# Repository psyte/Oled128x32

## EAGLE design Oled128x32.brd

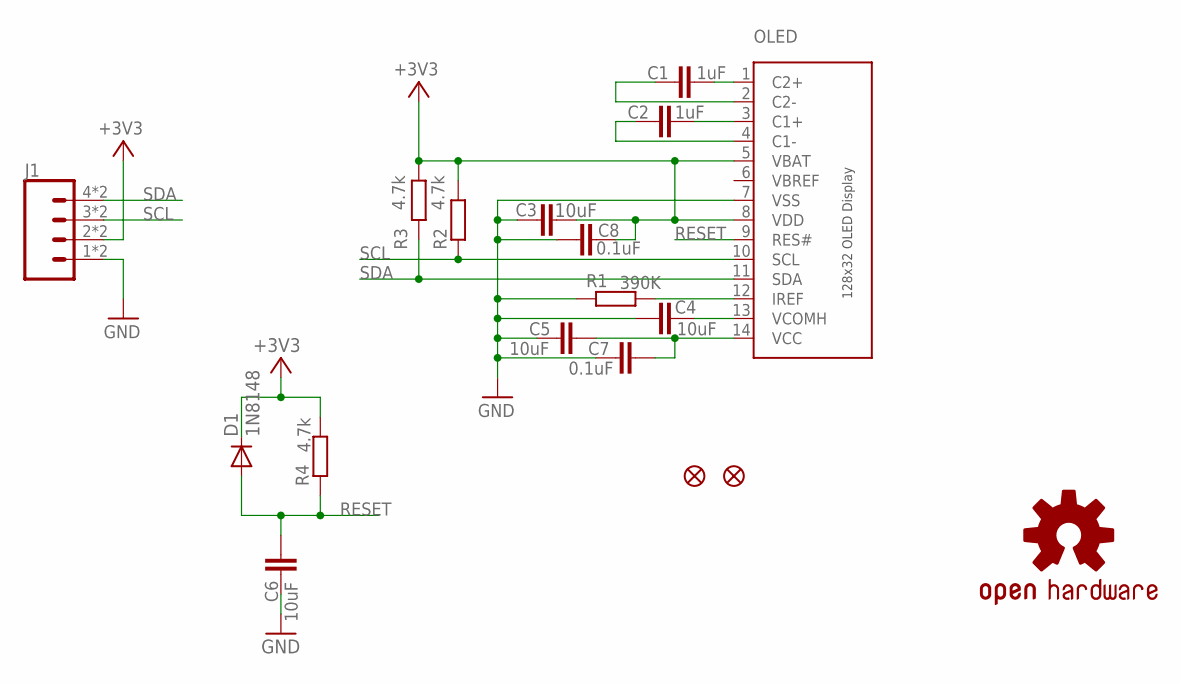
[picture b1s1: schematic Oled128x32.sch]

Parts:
C1, C2: 1uF; C0603
C3, C4, C5, C6: 10uF; C0603
C7, C8: 0.1uF; C0603
D1: 1N8148; SOD110-W
FD1, FD2: FIDUCIAL1X2; FIDUCIAL-1X2
J1: 1X04_SMD_STRAIGHT_COMBO; 1X04_SMD_VERTICAL_COMBO
LOGO1: OSHW-LOGOS; OSHW-LOGO-S
OLED: OLED_128X32_UG-2832HSWEG02; OLED_128X32_UG-2832HSWEG02_WRAPUNDER
R1: 390K; R0603
R2, R3, R4: 4.7k; R0603

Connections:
+3V3: C3.2, C8.2, D1.C, J1.2, J1.2-2 (2), OLED.5 (VBAT), OLED.8 (VDD), R2.2, R3.2, R4.2
GND: C3.1, C4.1, C5.1, C6.1, C7.1, C8.1, J1.1, J1.1-2 (1), OLED.7 (VSS), R1.1
unnamed: C1.2, OLED.1 (C2+)
unnamed: C1.1, OLED.2 (C2-)
unnamed: C2.2, OLED.3 (C1+)
unnamed: C2.1, OLED.4 (C1-)
unnamed: C4.2, OLED.13 (VCOMH)
unnamed: C5.2, C7.2, OLED.14 (VCC)
unnamed: OLED.12 (IREF), R1.2
RESET: C6.2, D1.A, OLED.9 (RES#), R4.1
SCL: J1.3, J1.3-2 (3), OLED.10 (SCL), R2.1
SDA: J1.4, J1.4-2 (4), OLED.11 (SDA), R3.1
VBREF: OLED.6 (VBREF)

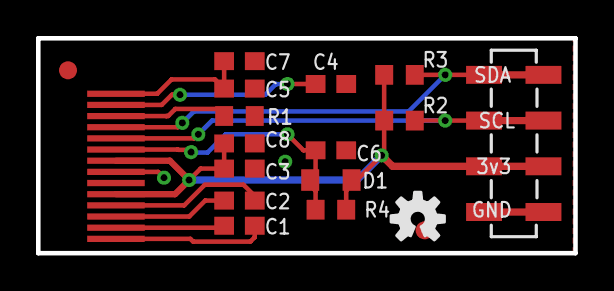
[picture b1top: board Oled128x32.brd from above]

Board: 2 copper layers, 29.8 x 11.9 mm, 18 parts (1 on the bottom side), 12 nets.

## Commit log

2018-12-28 gitignore: remove *.xln
2019-05-09 New gerber generated

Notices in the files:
parts and their libraries:
SparkFun-Connectors: Licensing: Creative Commons ShareAlike 4.0 International - https://creativecommons.org/licenses/by-sa/4.0
